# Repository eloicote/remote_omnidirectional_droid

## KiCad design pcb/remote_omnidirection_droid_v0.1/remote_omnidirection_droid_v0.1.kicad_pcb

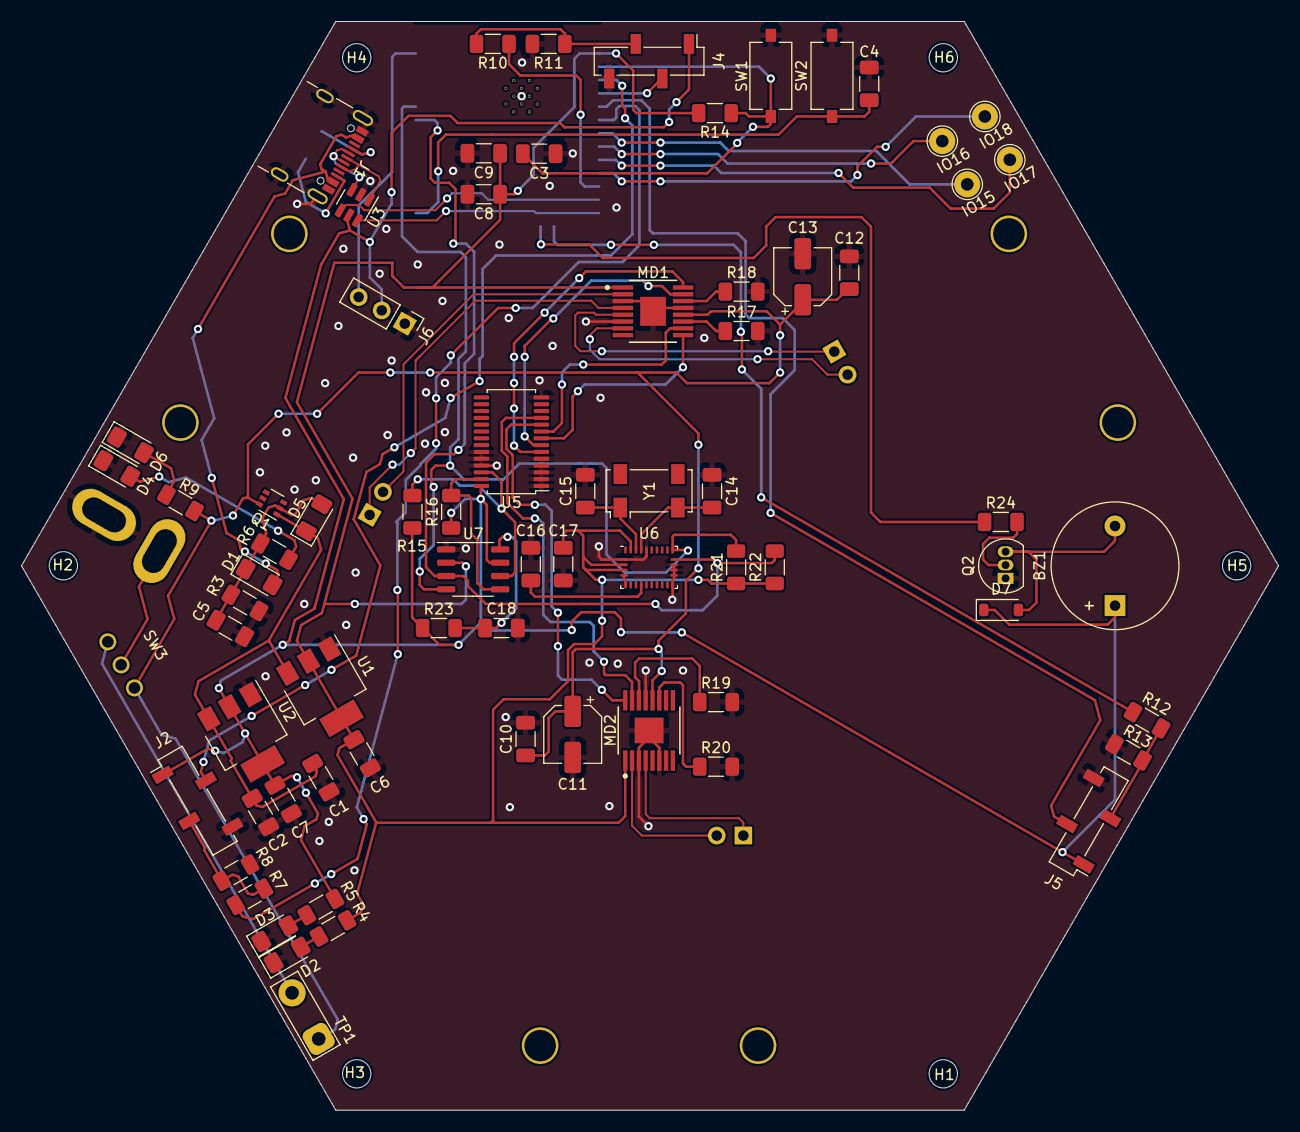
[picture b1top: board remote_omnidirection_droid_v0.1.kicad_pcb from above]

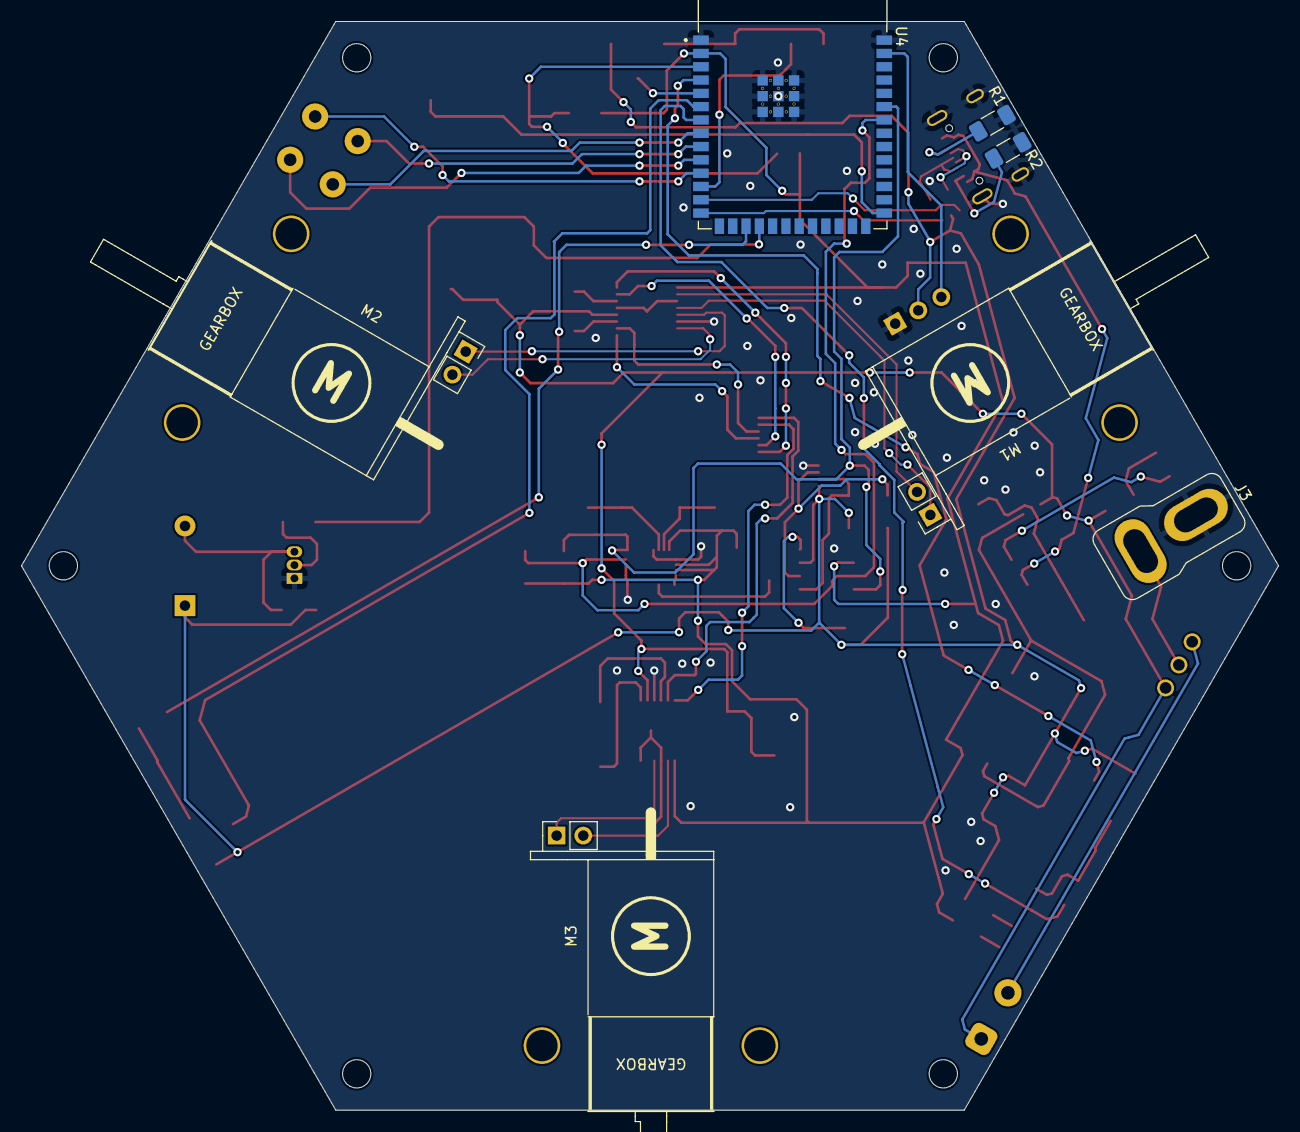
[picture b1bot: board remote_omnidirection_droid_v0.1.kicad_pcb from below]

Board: 2 copper layers, 120.0 x 103.9 mm, 85 parts (7 on the bottom side), 62 nets.

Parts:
BZ1: Buzzer; Buzzer_12x9.5RM7.6
C1, C2, C6, C7, C9, C14, C15: 22u; C_1206_3216Metric_Pad1.33x1.80mm_HandSolder
C3, C4, C8, C16, C17: 0.1u; C_1206_3216Metric_Pad1.33x1.80mm_HandSolder
C5, C18: 10u; C_1206_3216Metric_Pad1.33x1.80mm_HandSolder
C10, C12: 100n; C_1206_3216Metric_Pad1.33x1.80mm_HandSolder
C11, C13: 10u; CP_Elec_5x5.3
D1, D5: MSK4005; D_1206_3216Metric_Pad1.42x1.75mm_HandSolder
D2, D3, D4, D6: LED; LED_1206_3216Metric_Pad1.42x1.75mm_HandSolder
D7: 1N4148W; D_SOD-123
H1, H2, H3, H4, H5, H6: MountingHole; MountingHole_2.7mm_M2.5
IO15, IO16, IO17, IO18: TestPoint; TestPoint_THTPad_D2.5mm_Drill1.2mm
J1: USB_C_Receptacle_USB2.0; USB_C_Receptacle_GCT_USB4105-xx-A_16P_TopMnt_Horizontal
J2, J4, J5: Conn_01x04; PinSocket_1x04_P2.54mm_Vertical_SMD_Pin1Left
J3: BATT_CONNECT; Deans T-Plug Header
J6: Conn_01x03; PinHeader_1x03_P2.54mm_Vertical
M1, M2, M3: Motor_DC_ALT; Pimoroni_Motor_Breakout
MD1, MD2: DRV8411; PWP0016C-IPC_A
Q1: BC846BS; SOT-363_SC-70-6
Q2: 2N2219; TO-92L_Inline
R1, R2: 5.1k; R_1206_3216Metric_Pad1.30x1.75mm_HandSolder
R3: 100k; R_1206_3216Metric_Pad1.30x1.75mm_HandSolder
R4, R5, R6, R9: 220; R_1206_3216Metric_Pad1.30x1.75mm_HandSolder
R7, R8, R10, R11, R12, R13, R14, R15, R16, R21, R22: 10k; R_1206_3216Metric_Pad1.30x1.75mm_HandSolder
R17, R18, R19, R20: 22k; R_1206_3216Metric_Pad1.30x1.75mm_HandSolder
R23: 200k; R_1206_3216Metric_Pad1.30x1.75mm_HandSolder
R24: 180; R_1206_3216Metric_Pad1.30x1.75mm_HandSolder
SW1, SW2: SW_SPST; SW_Tactile_SPST_NO_Straight_CK_PTS636Sx25SMTRLFS
SW3: SW_SPDT; SWITCH_25336NA_APM
TP1: AMMETER_CONN; TestPoint_2Pads_Pitch5.08mm_Drill1.3mm
U1: AZ1117-3.3; SOT-223-3_TabPin2
U2: AZ1117-5.0; SOT-223-3_TabPin2
U3: USBLC6-2SC6; SOT-23-6
U4: ESP32-S3-WROOM-2-N32R8V; XCVR_ESP32-S3-WROOM-2-N32R8V
U5: PCA9685PW; TSSOP-28_4.4x9.7mm_P0.65mm
U6: BNO055; LGA-28_5.2x3.8mm_P0.5mm
U7: PCA9306D; SO-8_3.9x4.9mm_P1.27mm
Y1: 32.768kHz; Crystal_SMD_Abracon_ABS25-4Pin_8.0x3.8mm

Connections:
+3V3: C6.1, C8.1, C9.1, C17.2, MD1.1 (VREF), MD2.1 (VREF), R4.1, R14.2, R21.1, R22.1, U1.2 (VO), U4.2 (3V3), U6.3 (VDD), U6.4 (~BOOT_LOAD_PIN), U6.28 (VDDIO), U7.2 (VREF1)
+5V: BZ1.1 (-), C7.1, D7.1 (K), J2.1, J4.1, J5.1, J6.2, R5.1, R15.1, R16.1, R23.1, U2.2 (VO), U3.5 (VBUS), U5.28 (VDD), U7.7 (VREF2)
+BATT: C10.1, C11.1, C12.1, C13.1, MD1.12 (VM), MD2.12 (VM), Q1.6 (C1), R9.1, SW3.3 (C), TP1.1
/BOOT: C4.1, SW2.2 (B), U4.27 (IO0)
/BUZZER: R24.1, U4.18 (IO10)
/CC1: J1.A5 (CC1), R1.1
/CC2: J1.B5 (CC2), R2.1
/D+: U3.6 (I/O1), U4.14 (IO20)
/D-: U3.4 (I/O2), U4.13 (IO19)
/ECHO1: R7.1, U4.7 (IO7)
/ECHO2: R10.1, U4.12 (IO8)
/ECHO3: R12.1, U4.17 (IO9)
/EN: C3.1, R14.1, SW1.2 (B), U4.3 (EN)
/IO15: IO15.1, U4.8 (IO15)
/IO16: IO16.1, U4.9 (IO16)
/IO17: IO17.1, U4.10 (IO17)
/IO18: IO18.1, U4.11 (IO18)
/MOTOR1+: M1.1 (+), MD1.4 (AOUT2)
/MOTOR1-: M1.2 (-), MD1.2 (AOUT1)
/MOTOR2+: M2.1 (+), MD1.5 (BOUT2)
/MOTOR2-: M2.2 (-), MD1.7 (BOUT1)
/MOTOR3+: M3.1 (+), MD2.4 (AOUT2)
/MOTOR3-: M3.2 (-), MD2.2 (AOUT1)
/NESD_D+: J1.A6 (D+), J1.B6 (D+), U3.1 (I/O1)
/NESD_D-: J1.A7 (D-), J1.B7 (D-), U3.3 (I/O2)
/NeoPixel: J6.3, U4.39 (IO1)
/PWM1: MD1.16 (AIN1), U5.6 (LED0)
/PWM2: MD1.15 (AIN2), U5.7 (LED1)
/PWM3: MD1.9 (BIN1), U5.8 (LED2)
/PWM4: MD1.10 (BIN2), U5.9 (LED3)
/PWM5: MD2.16 (AIN1), U5.10 (LED4)
/PWM6: MD2.15 (AIN2), U5.11 (LED5)
/SCL: R22.2, U4.34 (IO41), U6.19 (COM1), U7.3 (SCL1)
/SCL_5V: R15.2, U5.26 (SCL), U7.6 (SCL2)
/SDA: R21.2, U4.35 (IO42), U6.20 (COM0), U7.4 (SDA1)
/SDA_5V: R16.2, U5.27 (SDA), U7.5 (SDA2)
/TRIG1: J2.2, U4.4 (IO4)
/TRIG2: J4.2, U4.5 (IO5)
/TRIG3: J5.2, U4.6 (IO6)
GND: C1.2, C2.2, C3.2, C4.2, C5.1, C6.2, C7.2, C8.2, C9.2, C10.2, C11.2, C12.2, C13.2, C14.2, C15.2, C16.2, C17.1, C18.2, D2.1 (K), D3.1 (K), D4.1 (K), D6.1 (K), J1.A1 (GND), J1.A12 (GND), J1.B1 (GND), J1.B12 (GND), J1.S1 (SHIELD), J2.4, J3.2, J4.4, J5.4, J6.1, MD1.3 (PGNDA), MD1.6 (PGNDB), MD1.13 (GND), MD1.17 (PAD), MD2.3 (PGNDA), MD2.6 (PGNDB), MD2.13 (GND), MD2.17 (PAD), Q2.1 (E), R1.2, R2.2, R3.1, R8.2, R11.2, R13.2, R17.2, R18.2, R19.2, R20.2, SW1.1 (A), SW2.1 (A), U1.1 (GND), U2.1 (GND), U3.2 (GND), U4.1 (GND), U4.40 (GND), U4.41_1 (GND), U4.41_2 (GND), U4.41_3 (GND), U4.41_4 (GND), U4.41_5 (GND), U4.41_6 (GND), U4.41_7 (GND), U4.41_8 (GND), U4.41_9 (GND), U5.1 (A0), U5.2 (A1), U5.3 (A2), U5.4 (A3), U5.5 (A4), U5.14 (VSS), U5.23 (~OE), U5.24 (A5), U5.25 (EXTCLK), U6.2 (GND), U6.5 (PS1), U6.6 (PS0), U6.15 (GNDIO), U6.16 (GNDIO), U6.17 (COM3), U6.18 (COM2), U6.25 (GNDIO), U7.1 (GND)
unnamed: BZ1.2 (+), D7.2 (A), Q2.3 (C)
unnamed: C5.2, D1.1 (K), D5.2 (A), Q1.2 (B1), R3.2, R6.1
unnamed: D2.2 (A), R4.2
unnamed: D3.2 (A), R5.2
unnamed: D4.2 (A), R6.2
unnamed: D6.2 (A), R9.2
unnamed: J2.3, R7.2, R8.1
unnamed: J3.1, SW3.2 (B)
unnamed: J4.3, R10.2, R11.1
unnamed: J5.3, R12.2, R13.1
unnamed: MD1.14 (AIPROPI), R18.1
unnamed: MD1.11 (BIPROPI), R17.1
unnamed: MD2.14 (AIPROPI), R19.1
unnamed: MD2.11 (BIPROPI), R20.1
unnamed: Q2.2 (B), R24.2
unnamed: SW3.1 (A), TP1.2
unnamed: C16.1, U6.9 (CAP)
unnamed: C15.1, U6.27 (XIN32), Y1.1
unnamed: C14.1, U6.26 (XOUT32), Y1.2
unnamed: C18.1, R23.2, U7.8 (EN)
VBUS: D1.2 (A), J1.A4 (VBUS), J1.A9 (VBUS), J1.B4 (VBUS), J1.B9 (VBUS)
VCC: C1.1, C2.1, D5.1 (K), Q1.1 (E1), U1.3 (VI), U2.3 (VI)

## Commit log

2024-05-10 ESP32-WROOM placed in schematic
2024-05-10 poorly designed a PCB
2024-05-13 updated PCB
2024-05-13 started adding MOTOR DRIVERS
2024-05-13 added motor drivers
2024-05-13 added BNO055
2024-05-14 board "complete"
2024-05-16 near finalized v0.1
